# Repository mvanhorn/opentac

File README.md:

# OpenTac

Design, build, read and simulate flex-PCB tactile sensors for any robot surface.

OpenTac-CAD turns a drawn outline, a DXF or SVG, or a surface of an STL part into a manufacturable
tactile sensor: a grid of taxels on a flex PCB, wired to a connector, with Gerbers, a printed
case and a manifest that describes the sensor. The same manifest configures the readout board,
the simulator and transfer between sensors.

**Website and docs:** https://opentac.github.io  ·  **Try it online:** https://opentac.github.io/cad/

## Quick start

You need [uv](https://docs.astral.sh/uv/getting-started/installation/) (the launchers offer to
install it).

```bash
git clone --depth 1 https://github.com/opentac/opentac opentac
cd opentac
uv run opentac cad          # design a sensor in your browser, locally
```

Or double-click `Start_OpenTac.command` (macOS) or `Start_OpenTac.bat` (Windows). On Linux, run
`bash Start_OpenTac.command`. The first run downloads what it needs, once.

With a readout board plugged in over USB:

```bash
uv run opentac flash                 # put the firmware on the board
uv run opentac setup my_design.zip   # tell the board which sensor is attached (once)
uv run opentac view                  # live heatmap
```

A new board has no firmware yet: hold its BOOT0 button while plugging it in, then run
`uv run opentac flash --board readout60` (or `node16` for the 30-pin pair). See
[Flash the firmware](https://opentac.github.io/use/flash/), which also covers Linux permissions.

```python
import opentac
sensor = opentac.Sensor()     # finds the board; it already knows its sensor
frame = sensor.read()         # one value per taxel; frame.image(sensor.manifest) lays it out
```

## Design with an AI agent

The repo ships a skill at `.claude/skills/opentac/`, which Claude Code loads automatically when
you open this folder. Other agents: see [AGENTS.md](AGENTS.md).

## Script a design

The skill's worked example builds a sensor without the browser:

```bash
uv run python .claude/skills/opentac/examples/insole.py insole_out
```

It draws a size 9 insole, checks the outline and generates the board: 200 taxels (10 columns x
28 rows) for the 60-pin readout board, DRC clean, in about 5 s on a laptop. `insole_out/` gets
the KiCad board, Gerbers, `manifest.json`, `design.json`, a preview SVG, a 1:1 printable PDF and
the cut files for the piezoresistive layer.

From your own script, call the function the web app's `/generate` route calls, as the skill's
helpers do (`.claude/skills/opentac/helpers/generate.py`):

```python
import base64
from opentac.cad import main

# Outline in mm, counter-clockwise; edge 0->1 is where the cable leaves.
resp = main.generate(main.GenerateRequest(
    outline=[[0, 0], [40, 0], [40, 30], [0, 30]],
    pixel_w_mm=3.0, pixel_h_mm=3.0, pitch_x_mm=3.5, pitch_y_mm=3.5,
    board_mode="expand", router="hug"))
print(resp.stats["total_pixels"], "taxels,", resp.drc["violations"], "DRC violations")

# The ZIP the web page downloads: board, Gerbers, manifest and the printed case.
full = main.zip_with_case_endpoint(main.ZipWithCaseRequest(zip_b64=resp.zip_b64, edit_data=resp.edit_data))
open("square.zip", "wb").write(base64.b64decode(full.zip_b64))
```

This prints `88 taxels, 0 DRC violations`, in about 2 s. `GenerateRequest` in
`opentac/cad/main.py` lists every parameter; [SKILL.md](.claude/skills/opentac/SKILL.md)
explains how to choose them.

## Simulate without a board

```python
from opentac import manifest, sim
m = manifest.load("examples/manifests/finger_8x6_60pin.json")
frame = sim.Sensor(m).press("sphere", force_n=5.0, radius_mm=5.0)   # 10 mm ball, 5 N
print(frame.image(m).round(2))                                      # newtons per taxel, as laid out
```

This is the foam model, for a skin with no bump sheet; it needs only numpy. The frame has the
same type a readout board returns. See [Simulation](https://opentac.github.io/sim/) for the bump
model, shear and ADC counts, and [Transfer](https://opentac.github.io/transfer/) for moving
frames between sensors.

## What is here

| Folder | Contents |
|---|---|
| `opentac/` | the Python package: CAD tool (`opentac.cad`), manifests, readout, viewer, simulation, transfer |
| `firmware/` | readout board firmware (60-pin and 30-pin boards) |
| `hardware/` | readout board KiCad files, fabrication files and BOMs |
| `examples/` | small manifests, example scripts, example STL parts, and the sources of the ready-to-order designs |
| `tests/` | the test suite (see [CONTRIBUTING.md](CONTRIBUTING.md)) |
| `scripts/` | maintenance: regenerate the example designs and board media, check the website against the package |
| `deploy/` | the Dockerfile for the hosted OpenTac-CAD backend (Render, configured in `render.yaml`) |

The website source is maintained separately in [opentac.github.io](https://github.com/opentac/opentac.github.io).

## Readout boards

| Board | Reads up to | Size |
|---|---|---|
| 60-pin | 30 rows x 30 columns | 37 x 34.3 mm |
| 30-pin (two stacked boards) | 15 rows x 15 columns | 16 x 22.8 mm |

Both plug straight into USB and carry an IMU. 30-pin boards can be daisy-chained over I2C,
behind a Teensy 4.0 ([Daisy chain](https://opentac.github.io/use/daisy-chain/)).
Where a command takes `--board`, the 60-pin board is `readout60` or `60pin`, the 30-pin pair
`node16` or `30pin`.

## Development

```bash
uv run --extra sim pytest -q     # about 6 min on a laptop
```

`--extra sim` installs MuJoCo, which four tests need. On a fresh clone 12 tests skip because they
need data that is not in the repository, and a few more without `node` or a C++ compiler.
[CONTRIBUTING.md](CONTRIBUTING.md) lists what each optional test needs, and how to report a
problem.

## Citing

See [CITATION.cff](CITATION.cff) and the [paper page](https://opentac.github.io/paper/).

## License

Code: MIT ([LICENSE](LICENSE)). Hardware designs: CERN-OHL-P-2.0 ([LICENSE-hardware](LICENSE-hardware)).
Documentation and media: CC BY 4.0 ([LICENSE-docs](LICENSE-docs)).
Third-party robot meshes in `examples/stl/` keep their own licenses, some of them non-commercial;
see [examples/stl/end_effectors/SOURCES.md](examples/stl/end_effectors/SOURCES.md).

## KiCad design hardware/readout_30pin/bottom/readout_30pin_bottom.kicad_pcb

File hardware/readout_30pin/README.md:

# 30-pin readout board pair

Reads one OpenTac sensor of up to **15 rows x 15 columns**. It is two small boards
stacked on 1.27 mm 7-pin header/socket pairs: the top board has the microcontroller,
the bottom board has the analog front end and the sensor connector.

| | Top board (`top/`) | Bottom board (`bottom/`) |
|---|---|---|
| Size | 16.0 x 22.8 mm, 4 layers | 16.0 x 22.7 mm, 2 layers |
| Main parts | STM32G431KBU6, LSM6DSV16BX IMU, micro-USB, two 4-pin JST SH I2C ports, RGB LED | ADG706 16-channel mux, two 74HC595, TLV9362 op-amp, LM2776 charge pump |
| Stacking | J1, J3: 1.27 mm 7-pin headers, underside | J2, J3: 1.27 mm 7-pin sockets, top side |
| Sensor connector | | Molex 505110-3091, 30-pin 0.5 mm FPC (LCSC C588008), underside. Pads 1-15 are columns, 16-30 are rows. |

Firmware target: `NODE16`.

## Files

Each folder has the same layout:

- the KiCad 10 project (`readout_30pin_top.*` or `readout_30pin_bottom.*`).
  Footprints, symbols and 3D models it uses are in [`hardware/libs`](../libs).
- `production/`: the JLCPCB fabrication files exported from this design on 2026-10-15: Gerber zip,
  JLCPCB BOM (`*_bom.csv`), pick-and-place positions (`*_positions.csv`), and the
  optional designator list and `netlist.ipc`.
- `bom.csv`: the same BOM with a manufacturer part number (MPN) column, for ordering parts elsewhere.

## Ordering from JLCPCB

Order the two boards separately.

1. Upload the Gerber zip as the PCB: `top/production/stm-i2c.zip` (4 layers) and
   `bottom/production/sensor_30.zip` (2 layers).
2. To have the parts fitted, turn on PCB Assembly and upload that board's
   `*_bom.csv` (BOM) and `*_positions.csv` (CPL). **Both boards have parts on both
   sides**, so choose two-sided assembly.
3. Check that each part shows as in stock before you pay. JLCPCB's stock changes daily.

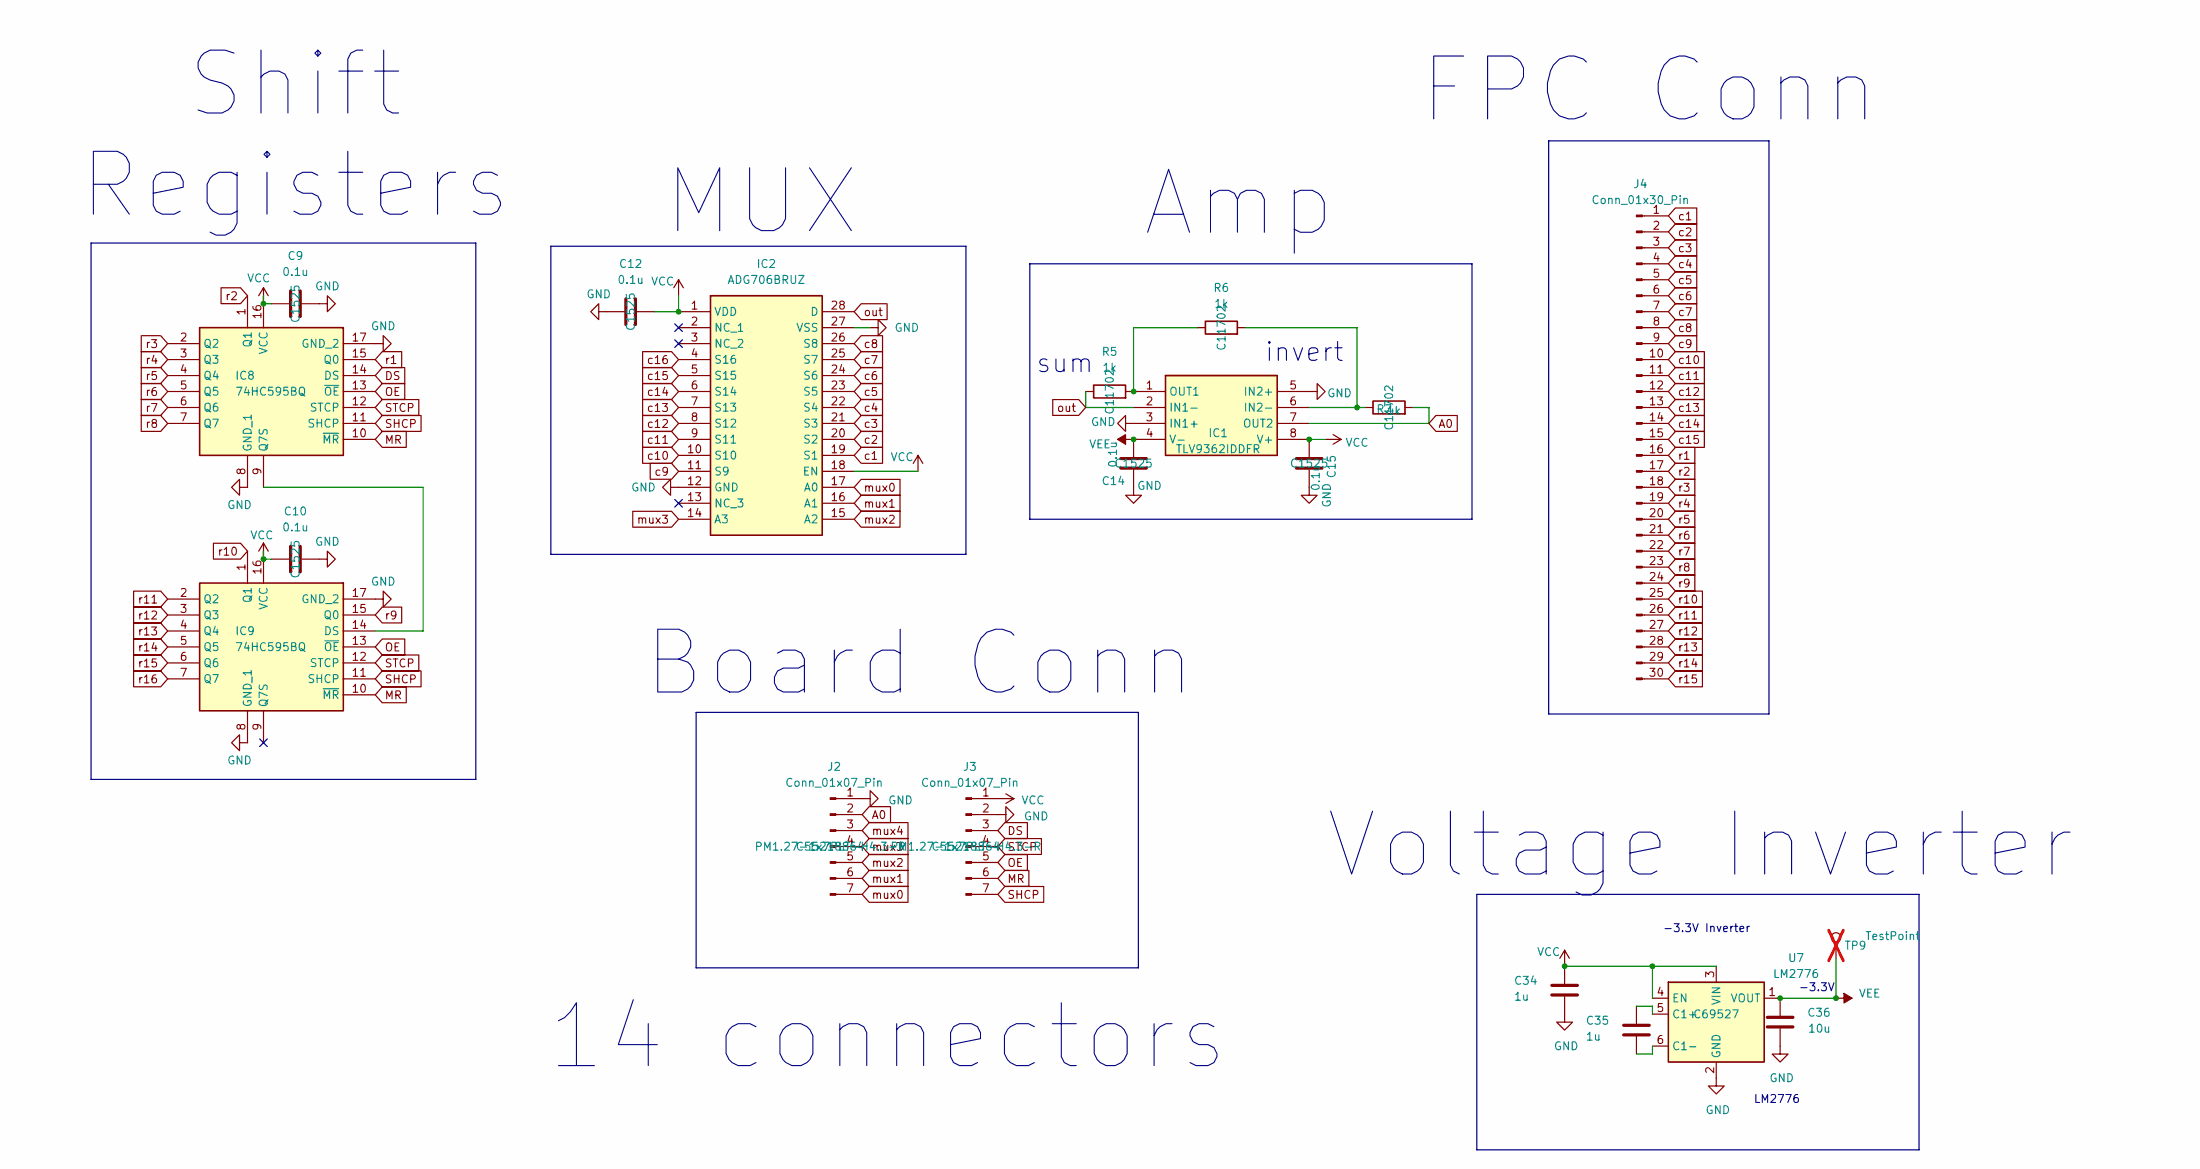
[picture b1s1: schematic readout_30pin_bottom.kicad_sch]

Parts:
C9, C10, C12, C14, C15: 0.1u; C_0402_1005Metric; LCSC Part # C1525
C34, C35: 1u; C_0402_1005Metric; LCSC Part # C52923
C36: 10u; C_0402_1005Metric; LCSC Part # C15525
IC1: TLV9362IDDFR; SOT65P280X110-8N; Manufacturer_Part_Number TLV9362IDDFR; LCSC Part # C5119287
IC2: ADG706BRUZ; SOP65P638X110-28N; Manufacturer_Part_Number ADG706BRUZ; LCSC Part # C579088
IC8, IC9: 74HC595BQ; NVT2006BQ115; Manufacturer_Part_Number 74HC595BQ; LCSC Part # C730243
J2, J3: Conn_01x07_Pin; PinSocket_1x07_P1.27mm_Vertical_SMD_Pin1Right; Manufacturer Part PM1.27-1x7PLT-H4.3-R; LCSC Part # C55218864
J4: Conn_01x30_Pin; CON_5051103091_MOL; Manufacturer_Part_Number 5051103091; LCSC Part # C588008
R5, R6, R7: 1k; R_0402_1005Metric; LCSC Part # C11702
TP9: TestPoint; TestPoint_Pad_1.0x1.0mm; not fitted
U7: LM2776; SOT-23-6; LCSC Part # C69527

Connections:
A0: IC1.7 (OUT2), J2.2, R7.2
DS: IC8.14 (DS), J3.3
GND: C9.2, C10.2, C12.2, C14.2, C15.2, C34.2, C36.2, IC1.3 (IN1+), IC1.5 (IN2+), IC2.12 (GND), IC2.27 (VSS), IC8.8 (GND_1), IC8.17 (GND_2), IC9.8 (GND_1), IC9.17 (GND_2), J2.1, J3.2, U7.2 (GND)
MR: IC8.10 (~MR), IC9.10 (~MR), J3.6
unnamed: IC1.6 (IN2-), R6.2, R7.1
unnamed: IC1.1 (OUT1), R5.2, R6.1
unnamed: IC8.9 (Q7S), IC9.14 (DS)
unnamed: C35.1, U7.5 (C1+)
unnamed: C35.2, U7.6 (C1-)
OE: IC8.13 (~OE), IC9.13 (~OE), J3.5
SHCP: IC8.11 (SHCP), IC9.11 (SHCP), J3.7
STCP: IC8.12 (STCP), IC9.12 (STCP), J3.4
VCC: C9.1, C10.1, C12.1, C15.1, C34.1, IC1.8 (V+), IC2.1 (VDD), IC2.18 (EN), IC8.16 (VCC), IC9.16 (VCC), J3.1, U7.3 (VIN), U7.4 (EN)
VEE: C14.1, C36.1, IC1.4 (V-), TP9.1, U7.1 (VOUT)
c1: IC2.19 (S1), J4.1
c2: IC2.20 (S2), J4.2
c3: IC2.21 (S3), J4.3
c4: IC2.22 (S4), J4.4
c5: IC2.23 (S5), J4.5
c6: IC2.24 (S6), J4.6
c7: IC2.25 (S7), J4.7
c8: IC2.26 (S8), J4.8
c9: IC2.11 (S9), J4.9
c10: IC2.10 (S10), J4.10
c11: IC2.9 (S11), J4.11
c12: IC2.8 (S12), J4.12
c13: IC2.7 (S13), J4.13
c14: IC2.6 (S14), J4.14
c15: IC2.5 (S15), J4.15
c16: IC2.4 (S16)
mux0: IC2.17 (A0), J2.7
mux1: IC2.16 (A1), J2.6
mux2: IC2.15 (A2), J2.5
mux3: IC2.14 (A3), J2.4
mux4: J2.3
out: IC1.2 (IN1-), IC2.28 (D), R5.1
r1: IC8.15 (Q0), J4.16
r2: IC8.1 (Q1), J4.17
r3: IC8.2 (Q2), J4.18
r4: IC8.3 (Q3), J4.19
r5: IC8.4 (Q4), J4.20
r6: IC8.5 (Q5), J4.21
r7: IC8.6 (Q6), J4.22
r8: IC8.7 (Q7), J4.23
r9: IC9.15 (Q0), J4.24
r10: IC9.1 (Q1), J4.25
r11: IC9.2 (Q2), J4.26
r12: IC9.3 (Q3), J4.27
r13: IC9.4 (Q4), J4.28
r14: IC9.5 (Q5), J4.29
r15: IC9.6 (Q6), J4.30
r16: IC9.7 (Q7)

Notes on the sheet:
LM2776
-3.3V
-3.3V Inverter
Board Conn
sum
MUX
Voltage Inverter
FPC Conn
Amp
invert
Shift Registers
14 connectors

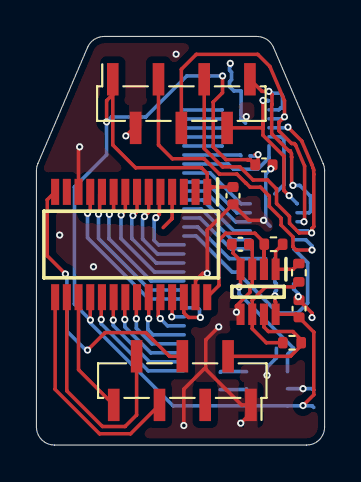
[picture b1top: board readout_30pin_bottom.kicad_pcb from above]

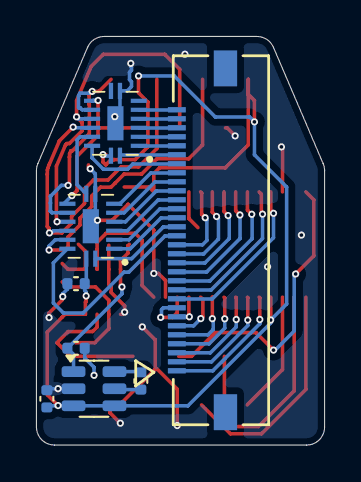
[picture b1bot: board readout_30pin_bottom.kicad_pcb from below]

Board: 2 copper layers, 16.0 x 22.7 mm, 19 parts (8 on the bottom side), 49 nets.

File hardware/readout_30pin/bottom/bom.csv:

Designator,Footprint,Quantity,Value,LCSC Part #,MPN
"C10, C12, C14, C15, C9",0402,5,0.1u,C1525,CL05B104KO5NNNC
"C34, C35",0402,2,1u,C52923,CL05A105KA5NQNC
C36,0402,1,10u,C15525,CL05A106MQ5NUNC
IC1,SOT65P280X110-8N,1,TLV9362IDDFR,C5119287,TLV9362IDDFR
IC2,SOP65P638X110-28N,1,ADG706BRUZ,C579088,ADG706BRUZ
"IC8, IC9",NVT2006BQ115,2,74HC595BQ,C730243,74HC595BQ
"J2, J3",PinSocket_1x07_P1.27mm_Vertical_SMD_Pin1Right,2,Conn_01x07_Pin,C55218864,PM1.27-1x7PLT-H4.3-R
J4,CON_5051103091_MOL,1,Conn_01x30_Pin,C588008,5051103091
"R5, R6, R7",0402,3,1k,C11702,0402WGF1001TCE
U7,SOT-23-6,1,LM2776,C69527,LM2776DBVR

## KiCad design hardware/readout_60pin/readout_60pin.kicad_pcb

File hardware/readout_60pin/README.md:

# 60-pin readout board

Reads one OpenTac sensor of up to **30 rows x 30 columns**. This is the
"I2C gain switch" version: the gain is set in firmware, with no jumpers.

| | |
|---|---|
| Size | 37.0 x 34.3 mm, 4 layers, 1.6 mm thick |
| Sensor connector | Molex 505110-6091, 60-pin 0.5 mm FPC (LCSC C493444). Pads 1-30 are rows, 31-60 are columns. |
| Microcontroller | STM32G431KBU6 |
| Gain | MAX14662 I2C switch (address 0x4C) puts 4.7k, 1.1k, 270 or 68 ohm in parallel with the 10k base resistor |
| Other | LSM6DSV16BX IMU (I2C 0x6A), micro-USB, two 4-pin JST SH I2C ports, RGB LED, Tag-Connect TC2030 for SWD |
| Firmware target | `READOUT60` |

## Files

- `readout_60pin.kicad_pro`, `.kicad_sch`, `.kicad_pcb`: the KiCad 10 project.
  Footprints, symbols and 3D models it uses are in [`../libs`](../libs).
- `production/`: the JLCPCB fabrication files exported from this design on 2026-10-15.
  - `stm-i2c-60-switch.zip`: Gerbers and drill files
  - `stm-i2c-60-switch_bom.csv`: bill of materials, JLCPCB format (LCSC part numbers)
  - `stm-i2c-60-switch_positions.csv`: pick-and-place positions
  - `stm-i2c-60-switch_designators.csv`, `netlist.ipc`: optional extras (designator list, IPC-D-356 netlist for electrical test)
- `bom.csv`: the same BOM with a manufacturer part number (MPN) column, for ordering parts elsewhere.

The schematic also holds parts that are not on this PCB and not in the BOM:
U9 (digipot), JP1-JP4, R8, R9, C46-C49, C51, H1-H4 and TP9.

## Ordering from JLCPCB

1. Upload `production/stm-i2c-60-switch.zip` as the PCB. It is a 4-layer board.
2. To have the parts fitted, turn on PCB Assembly and upload
   `production/stm-i2c-60-switch_bom.csv` (BOM) and
   `production/stm-i2c-60-switch_positions.csv` (CPL). All parts are on the top side.
3. Check that each part shows as in stock before you pay. JLCPCB's stock changes daily.

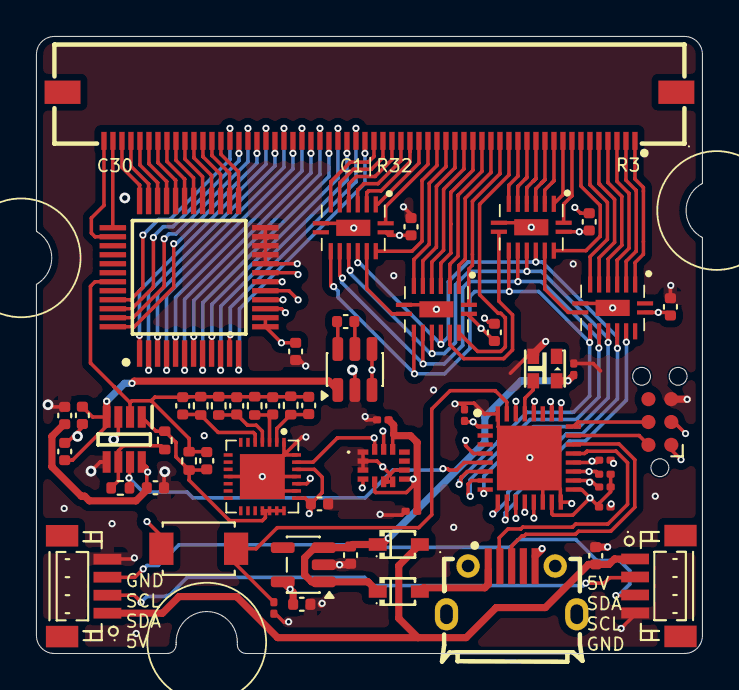
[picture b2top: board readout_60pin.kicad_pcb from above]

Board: 4 copper layers, 37.0 x 34.3 mm, 55 parts (0 on the bottom side), 101 nets.

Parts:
C1, C9, C10, C13, C14, C15, C17, C60: 0.1u; C_0402_1005Metric
C2, C3, C16, C31, C32: 0.1u; C_0201_0603Metric
C28, C36, C38, C39: 10u; C_0402_1005Metric
C34, C35: 1u; C_0402_1005Metric
C52: 47p; C_0402_1005Metric
C54: 100p; C_0402_1005Metric
C55: 470p; C_0402_1005Metric
C57: 1.8n; C_0402_1005Metric
C59: 6.8n; C_0402_1005Metric
CN1, CN2: BM04B-SRSS-TB(LF)(SN); C160390_CONN-SMD_BM04B-SRSS-TB
D1, D3: 1N5819WS; C191023_SOD-323_L1_8-W1_3-LS2_5-RD
IC1: TLV9362IDDFR; SOT65P280X110-8N
IC3: STM32G431KBU6; QFN50P500X500X60-33N-D
IC4: ADG732BSUZ; QFP50P900X900X120-48N
IC5: LSM6DSV16BXTR
IC8, IC9, IC11, IC12: 74HC595BQ; NVT2006BQ115
J2: Conn_ARM_SWD_TagConnect_TC2030-NL; Tag-Connect_TC2030-IDC-NL_2x03_P1.27mm_Vertical
J4: 5051106091; C493444_FPC-SMD_5051106091
LED1: XL-2020RGBC-WS2812B; C5349955_LED-SMD_4P-L2_0-W2_0-BR-1
R4: 10k; R_0201_0603Metric
R6, R7: 1k; R_0402_1005Metric
R18: 100k; R_0201_0603Metric
R19, R20: 4.7k; R_0201_0603Metric
R21: 10k; R_0402_1005Metric
R23: 4.7k; R_0402_1005Metric
R24: 1.1k; R_0402_1005Metric
R26: 270; R_0402_1005Metric
R28: 68; R_0402_1005Metric
S4: TS-1088-AR02016; SW_TS-1088-AR02016
U1: TLV75533PDBV; SOT-23-5
U7: LM2776; SOT-23-6
U10: MAX14662ETI+T; C2673377_TQFN-28_L4_0-W4_0-P0_40-BL-EP
USB2: MicroXNJ; C404969_MICRO-USB-SMD_MICROXNJ_1

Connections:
5V: C28.1, CN1.1, CN2.1, D1.2 (A)
5V-led: C16.1, C39.1, D1.1 (K), D3.1 (K), LED1.4 (VDD), U1.1 (IN), U1.3 (EN)
/FB1: C54.2, R23.2, U10.2 (A1)
/FB2: C55.2, R24.2, U10.3 (A2)
/FB3: C57.2, R26.2, U10.4 (A3)
/FB4: C59.2, R28.2, U10.5 (A4)
/TIA_OUT: C52.2, IC1.1 (OUT1), R6.1, R21.2, U10.18 (B4), U10.19 (B3), U10.20 (B2), U10.21 (B1)
A0: IC1.7 (OUT2), IC3.5 (PA0), R7.2
D+: IC3.22 (PA12), USB2.3 (D+)
D-: IC3.21 (PA11), USB2.2 (D-)
DS: IC3.10 (PA5), IC8.14 (DS)
GND: C1.2, C2.1, C3.1, C9.2, C10.2, C13.2, C14.2, C15.2, C16.2, C17.2, C28.2, C31.2, C32.2, C34.2, C36.2, C38.2, C39.2, C60.2, CN1.4, CN2.4, IC1.3 (IN1+), IC1.5 (IN2+), IC3.14 (VSSA), IC3.16 (VSS_1), IC3.32 (VSS_2), IC3.33 (EP), IC4.20 (~CS), IC4.21 (~WR), IC4.22 (~EN), IC4.23 (GND), IC4.24 (VSS), IC5.1 (SDO/SA0), IC5.2 (TDMOUT), IC5.3 (BCLK), IC5.6 (AH1/QVAR1), IC5.7 (GND), IC5.9 (AH2/QVAR2), IC8.8 (GND_1), IC8.17 (GND_2), IC9.8 (GND_1), IC9.17 (GND_2), IC11.8 (GND_1), IC11.17 (GND_2), IC12.8 (GND_1), IC12.17 (GND_2), J2.5 (GND), LED1.2 (GND), R4.1, R18.2, U1.2 (GND), U7.2 (GND), U10.1 (SPI/I2C#), U10.11 (GND), U10.23 (CS#/AD0), U10.25 (GND), U10.28 (DOUT/AD1), U10.29 (EP), USB2.5 (GND)
IMU_INT: IC3.13 (PB0), IC5.4 (INT1)
MR: IC3.6 (PA1), IC8.10 (~MR), IC9.10 (~MR), IC11.10 (~MR), IC12.10 (~MR)
NRST: IC3.4 (PG10-NRST), J2.3 (~RESET)
unnamed: IC1.6 (IN2-), R6.2, R7.1
unnamed: IC3.29 (PB6), LED1.3 (DI)
unnamed: IC3.31 (PB8-BOOT0), R4.2, S4.2
unnamed: IC8.9 (Q7S), IC9.14 (DS)
unnamed: IC9.9 (Q7S), IC11.14 (DS)
unnamed: IC11.9 (Q7S), IC12.14 (DS)
unnamed: C35.1, U7.5 (C1+)
unnamed: C35.2, U7.6 (C1-)
OE: IC3.9 (PA4), IC8.13 (~OE), IC9.13 (~OE), IC11.13 (~OE), IC12.13 (~OE)
SCL: IC3.19 (PA9), IC5.13 (SCL), R20.2, U10.24 (SCLK/SCL)
SDA: IC3.18 (PA8), IC5.14 (SDA), R19.2, U10.27 (DIN/SDA)
SHCP: IC3.7 (PA2), IC8.11 (SHCP), IC9.11 (SHCP), IC11.11 (SHCP), IC12.11 (SHCP)
STCP: IC3.8 (PA3), IC8.12 (STCP), IC9.12 (STCP), IC11.12 (STCP), IC12.12 (STCP)
SWCLK: IC3.24 (PA14), J2.4 (SWCLK)
SWDIO: IC3.23 (PA13), J2.2 (SWDIO)
VBUS: D3.2 (A), USB2.1 (VBUS)
VCC: C1.1, C2.2, C3.2, C9.1, C10.1, C13.1, C15.1, C17.1, C31.1, C32.1, C34.1, C38.1, C60.1, IC1.8 (V+), IC3.1 (VDD_1), IC3.15 (VDDA), IC3.17 (VDD_2), IC4.13 (VDD_1), IC4.14 (VDD_2), IC5.5 (VDD_IO), IC5.8 (VDD), IC5.12 (CS), IC8.16 (VCC), IC9.16 (VCC), IC11.16 (VCC), IC12.16 (VCC), J2.1 (VCC), R19.1, R20.1, S4.1, U1.5 (OUT), U7.3 (VIN), U7.4 (EN), U10.22 (SD#), U10.26 (VCC)
VEE: C14.1, C36.1, IC1.4 (V-), U7.1 (VOUT)
c1: IC4.12 (S1), J4.31
c2: IC4.11 (S2), J4.32
c3: IC4.10 (S3), J4.33
c4: IC4.9 (S4), J4.34
c5: IC4.8 (S5), J4.35
c6: IC4.7 (S6), J4.36
c7: IC4.6 (S7), J4.37
c8: IC4.5 (S8), J4.38
c9: IC4.4 (S9), J4.39
c10: IC4.3 (S10), J4.40
c11: IC4.2 (S11), J4.41
c12: IC4.1 (S12), J4.42
c13: IC4.48 (S13), J4.43
c14: IC4.47 (S14), J4.44
c15: IC4.46 (S15), J4.45
c16: IC4.45 (S16), J4.46
c17: IC4.25 (S17), J4.47
c18: IC4.26 (S18), J4.48
c19: IC4.27 (S19), J4.49
c20: IC4.28 (S20), J4.50
c21: IC4.29 (S21), J4.51
c22: IC4.30 (S22), J4.52
c23: IC4.31 (S23), J4.53
c24: IC4.32 (S24), J4.54
c25: IC4.33 (S25), J4.55
c26: IC4.34 (S26), J4.56
c27: IC4.35 (S27), J4.57
c28: IC4.36 (S28), J4.58
c29: IC4.37 (S29), J4.59
c30: IC4.38 (S30), J4.60
mux0: IC3.11 (PA6), IC4.15 (A0)
mux1: IC3.12 (PA7), IC4.16 (A1)
mux2: IC3.20 (PA10), IC4.17 (A2), R18.1
mux3: IC3.26 (PB3), IC4.18 (A3)
mux4: IC3.28 (PB5), IC4.19 (A4)
out: C52.1, C54.1, C55.1, C57.1, C59.1, IC1.2 (IN1-), IC4.43 (D), R21.1, R23.1, R24.1, R26.1, R28.1
r3: IC8.2 (Q2), J4.1
r4: IC8.3 (Q3), J4.2
r5: IC8.4 (Q4), J4.3
r6: IC8.5 (Q5), J4.4
r7: IC8.6 (Q6), J4.5
r8: IC8.7 (Q7), J4.6
r9: IC9.15 (Q0), J4.7
r10: IC9.1 (Q1), J4.8
r11: IC9.2 (Q2), J4.9
r12: IC9.3 (Q3), J4.10
r13: IC9.4 (Q4), J4.11
r14: IC9.5 (Q5), J4.12
r15: IC9.6 (Q6), J4.13
r16: IC9.7 (Q7), J4.14
r17: IC11.15 (Q0), J4.15
r18: IC11.1 (Q1), J4.16
r19: IC11.2 (Q2), J4.17
r20: IC11.3 (Q3), J4.18
r21: IC11.4 (Q4), J4.19
r22: IC11.5 (Q5), J4.20
r23: IC11.6 (Q6), J4.21
r24: IC11.7 (Q7), J4.22
r25: IC12.15 (Q0), J4.23
r26: IC12.1 (Q1), J4.24
r27: IC12.2 (Q2), J4.25
r28: IC12.3 (Q3), J4.26
r29: IC12.4 (Q4), J4.27
r30: IC12.5 (Q5), J4.28
r31: IC12.6 (Q6), J4.29
r32: IC12.7 (Q7), J4.30
scl-bus: CN1.3, CN2.3, IC3.25 (PA15)
sda-bus: CN1.2, CN2.2, IC3.30 (PB7)

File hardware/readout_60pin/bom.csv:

Designator,Footprint,Quantity,Value,LCSC Part #,MPN
"C1, C10, C13, C14, C15, C17, C60, C9",0402,8,0.1u,C1525,CL05B104KO5NNNC
"C16, C2, C3, C31, C32",0201,5,0.1u,C49062,CL03A104KP3NNNC
"C28, C36, C38, C39",0402,4,10u,C15525,CL05A106MQ5NUNC
"C34, C35",0402,2,1u,C52923,CL05A105KA5NQNC
C52,0402,1,47p,C1567,0402CG470J500NT
C54,0402,1,100p,C1546,0402CG101J500NT
C55,0402,1,470p,C106259,CC0402JRNPO9BN471
C57,0402,1,1.8n,C385028,GRM1555C1H182JA01D
C59,0402,1,6.8n,C1518206,GRM1555C1H682JE01D
"CN1, CN2",C160390_CONN-SMD_BM04B-SRSS-TB,2,BM04B-SRSS-TB(LF)(SN),C160390,BM04B-SRSS-TB(LF)(SN)
"D1, D3",C191023_SOD-323_L1_8-W1_3-LS2_5-RD,2,1N5819WS,C191023,1N5819WS
IC1,SOT65P280X110-8N,1,TLV9362IDDFR,C5119287,TLV9362IDDFR
"IC11, IC12, IC8, IC9",NVT2006BQ115,4,74HC595BQ,C730243,74HC595BQ
IC3,QFN50P500X500X60-33N-D,1,STM32G431KBU6,C529358,STM32G431KBU6
IC4,QFP50P900X900X120-48N,1,ADG732BSUZ,C114845,ADG732BSUZ
IC5,LSM6DSV16BXTR,1,LSM6DSV16BXTR,C5267394,LSM6DSV16BXTR
J4,C493444_FPC-SMD_5051106091,1,5051106091,C493444,5051106091
LED1,C5349955_LED-SMD_4P-L2_0-W2_0-BR-1,1,XL-2020RGBC-WS2812B,C5349955,XL-2020RGBC-2812B
R18,0201,1,100k,C106224,RC0201FR-07100KL
"R19, R20",0201,2,4.7k,C138135,RC0201FR-074K7L
R21,0402,1,10k,C25744,0402WGF1002TCE
R23,0402,1,4.7k,C25900,0402WGF4701TCE
R24,0402,1,1.1k,C25860,0402WGF1101TCE
R26,0402,1,270,C25099,0402WGF2700TCE
R28,0402,1,68,C25131,0402WGF680JTCE
R4,0201,1,10k,C106225,RC0201FR-0710KL
"R6, R7",0402,2,1k,C11702,0402WGF1001TCE
S4,SW_TS-1088-AR02016,1,TS-1088-AR02016,C720477,TS-1088-AR02016
U1,SOT-23-5,1,TLV75533PDBV,C404027,TLV75533PDBVR
U10,C2673377_TQFN-28_L4_0-W4_0-P0_40-BL-EP,1,MAX14662ETI+T,C2673377,MAX14662ETI+T
U7,SOT-23-6,1,LM2776,C69527,LM2776DBVR
USB2,C404969_MICRO-USB-SMD_MICROXNJ_1,1,MicroXNJ,C404969,MicroXNJ

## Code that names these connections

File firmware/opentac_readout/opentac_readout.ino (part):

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// ----- Bus node build (-DOT_BUS_NODE) ----------------------------------------
//
// The same firmware as a node on the OpenTac bus: many boards behind one
// Teensy 4.0 on I2C1 (SCL PA15, SDA PB7), auto-addressed by SMBus ARP. Only
// the transport changes. The command lines above arrive over the bus
// instead of USB and the replies go back the same way, so provisioning,
// parameters and xampling are this file's code, not a copy of it. Frames are
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// description below is that of the 70-pin readout (READOUT32). The 60-pin
// board (READOUT60) has the same drive and mux, differs in its '595 pin order
// and adds a gain switch (GAIN_SW). The 30-pin board (NODE16) has two '595
// stages and a 16:1 mux on MUX0..MUX3; PB5 is not part of it.
//
// Drive: four cascaded 74HC595 stages, walked by a single travelling 1. Because
// the 1 can only shift forward, the scan visits steps in order and reads, at
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// it is the skin's columns that are driven.
//
// Sense: a 32:1 mux fed by MUX0..MUX4:
//   MUX0 = PA6, MUX1 = PA7, MUX2 = PA10, MUX3 = PB3, MUX4 = PB5,
// wired straight through to A0..A4. PB5 also carries CAN_RX on boards that
// populate the transceiver; leave CAN unused.
//
// The order of the lines comes from the config's row_order and col_order, so
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
// ----- Pinout ---------------------------------------------------------------

#define TACTILE_ADC  PA0
#if defined(OT_BOARD_READOUT60)
// The 60-pin board wires the '595 control lines to PA1..PA5 in a different
// order (read off its KiCad netlist at the '595 pins). The rest is the same.
#define SR_MR        PA1
#define SR_SHCP      PA2
#define SR_STCP      PA3
#define SR_OE        PA4
#define SR_DS        PA5
#define SR_MR_BIT    GPIO_PIN_1
#define SR_SHCP_BIT  GPIO_PIN_2
#define SR_STCP_BIT  GPIO_PIN_3
#define SR_DS_BIT    GPIO_PIN_5
#else
#define SR_DS        PA1
#define SR_OE        PA2
#define SR_STCP      PA3
#define SR_SHCP      PA4
#define SR_MR        PA5
#define SR_DS_BIT    GPIO_PIN_1
#define SR_STCP_BIT  GPIO_PIN_3
#define SR_SHCP_BIT  GPIO_PIN_4
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#endif
// The *_BIT masks are the same pins on GPIOA, for the direct BSRR writes the
// scan makes; keep the two lists in step.
#define MUX0_PIN     PA6
#define MUX1_PIN     PA7
#define MUX2_PIN     PA10
#define MUX3_PIN     PB3
#define MUX4_PIN     PB5
#define IMU_SDA      PA_8
#define IMU_SCL      PA_9
#define RGB_DATA     PB6
#if defined(OT_BUS_NODE)
#define BUS_SCL      PA15
#define BUS_SDA      PB7
#endif

// Sets the max source impedance the input can resolve; an untouched cell is far
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  }

  ADC_ChannelConfTypeDef channel = {};
  channel.Channel = ADC_CHANNEL_1;  // PA0 = ADC1_IN1
  channel.Rank = ADC_REGULAR_RANK_1;
  channel.SamplingTime = TACTILE_SAMPLE_TIME;
  channel.SingleDiff = ADC_SINGLE_ENDED;
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                ((channel & 0x02u) ? GPIO_PIN_7 : (GPIO_PIN_7 << 16)) |
                ((channel & 0x04u) ? GPIO_PIN_10 : (GPIO_PIN_10 << 16));
#if defined(OT_BOARD_NODE16)
  // 16:1 mux: MUX3 is the top address bit, and PB5 belongs to something else.
  GPIOB->BSRR = ((channel & 0x08u) ? GPIO_PIN_3 : (GPIO_PIN_3 << 16));
#else
  GPIOB->BSRR = (((channel & 0x08u) ? GPIO_PIN_3 : (GPIO_PIN_3 << 16)) |
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  rowsOff();
  digitalWrite(SR_OE, LOW);

  pinMode(MUX0_PIN, OUTPUT); digitalWrite(MUX0_PIN, LOW);
  pinMode(MUX1_PIN, OUTPUT); digitalWrite(MUX1_PIN, LOW);
  pinMode(MUX2_PIN, OUTPUT); digitalWrite(MUX2_PIN, LOW);
  pinMode(MUX3_PIN, OUTPUT); digitalWrite(MUX3_PIN, LOW);
#if !defined(OT_BOARD_NODE16)
  pinMode(MUX4_PIN, OUTPUT); digitalWrite(MUX4_PIN, LOW);
#endif

  pinMode(TACTILE_ADC, INPUT_ANALOG);
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  GPIOA->BSRR = SR_MR_BIT << 16;     // MR low
  __NOP(); __NOP(); __NOP(); __NOP();
  GPIOA->BSRR = SR_MR_BIT;           // MR high
  GPIOA->BSRR = SR_STCP_BIT << 16;     // STCP low
  GPIOA->BSRR = SR_DS_BIT;           // DS high
  __NOP(); __NOP();
  GPIOA->BSRR = SR_SHCP_BIT;           // SHCP rising
  __NOP(); __NOP(); __NOP();
  GPIOA->BSRR = SR_SHCP_BIT << 16;     // SHCP falling
  GPIOA->BSRR = SR_DS_BIT << 16;     // DS low: every later shift injects 0
  GPIOA->BSRR = SR_STCP_BIT;           // STCP high latches P0 active
}

// One clock walks the active bit to the next stage.
static inline void rowWalkAdvance() {
  GPIOA->BSRR = SR_STCP_BIT << 16;     // STCP low
  __NOP(); __NOP();
  GPIOA->BSRR = SR_SHCP_BIT;           // SHCP rising
  __NOP(); __NOP(); __NOP();
  GPIOA->BSRR = SR_SHCP_BIT << 16;     // SHCP falling
  __NOP(); __NOP();
  GPIOA->BSRR = SR_STCP_BIT;           // STCP high latches the next row
}

// The walking 1 only moves forward, so shift-register steps are visited in
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
static void xampWalkTo(uint8_t step) {
  uint8_t at = xampStep;
  GPIOA->BSRR = SR_STCP_BIT << 16;     // STCP low: outputs hold until the end
  if (at == 0xFF || step < at) {
    GPIOA->BSRR = SR_MR_BIT << 16;   // MR low: clear the shift register
    __NOP(); __NOP(); __NOP(); __NOP();
    GPIOA->BSRR = SR_MR_BIT;         // MR high
    GPIOA->BSRR = SR_DS_BIT;         // DS high
    __NOP(); __NOP();
    GPIOA->BSRR = SR_SHCP_BIT;         // SHCP rising: the 1 enters stage 0
    __NOP(); __NOP(); __NOP();
    GPIOA->BSRR = SR_SHCP_BIT << 16;   // SHCP falling
    GPIOA->BSRR = SR_DS_BIT << 16;   // DS low: every later shift injects 0
    at = 0;
  }
  while (at < step) {
    __NOP(); __NOP();
    GPIOA->BSRR = SR_SHCP_BIT;         // SHCP rising
    __NOP(); __NOP(); __NOP();
    GPIOA->BSRR = SR_SHCP_BIT << 16;   // SHCP falling
    ++at;
  }
  __NOP(); __NOP();
  GPIOA->BSRR = SR_STCP_BIT;           // STCP high: one latch, straight to `step`
  xampStep = step;
}
uint16_t xampRowSettleUs = 0;
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// ----- RGB ------------------------------------------------------------------

static void rgbBegin() {
  // PB6 doubles as UCPD1_CC1; clear its dead-battery pull-down explicitly.
#if defined(PWR_CR3_UCPD_DBDIS)
  SET_BIT(PWR->CR3, PWR_CR3_UCPD_DBDIS);
#endif
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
